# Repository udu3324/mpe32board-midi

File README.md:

# mpe32board-midi

An expressive midi controller that has onboard sound processing with an expandable and hackable nature.
(v2 of [stm32pe-midi](https://github.com/udu3324/stm32pe-midi))

 * Built in DSP
 * Support for Programs and Sequencer
 * Hacker Header Exposed GPIO
 * Micro-SD Card Support
 * Onboard SDRAM for extended recording/memory

## Purpose
After making the [stm32pe-midi](https://github.com/udu3324/stm32pe-midi), I wanted to reflect at the problems I faced and the feature set I sacrificed out of it originally. I wanted to learn how ram works and the correct way to implement it, which I did for this project. I also wanted something that was more polished and structured better as the pcb dictated the rest of the design which lead to unfortunate design decisions. I instead designed everything in module-like components to allow more expansion and flexibility in the future.

## Zine Page
Some information is redacted on this export, DM me for the full version!

## Firmware
The firmware uses the stm32cubemx software to generate a .ioc of its pinout functions and its cmake gcc code template. I then chose Visual Studio Code as the choice of my IDE to code the rest in C/C++.

There is sample code [here](https://gist.github.com/udu3324/de9aada8e3ea0addc13870c6bbbebc0f) for trying out the mpe32sensors standalone on the Arduino platform.

### Libraries Used
 * https://github.com/hathach/tinyusb
 * https://github.com/jtainer/i2c-mux
 * https://github.com/berndoJ/libneopixel32
 * https://github.com/devOramaMan/stm32_TMAG5273 (modified/fixed)
 * https://github.com/alixahedi/i2c-lcd-stm32

## CAD
### Case
The case is a 3 part 3d-printed case that is screwed together with m3 screws, both being self-tapped and heat-set inserts. There are two wood block accents (or plywood) on the side screwed in too.

Each key is press fit and can also be screwed in with a m3 screw and nut if needed.

Due to my 3d-printer being too small, I have to cut the board in half to print. This is later adhered with uv-glue.

### Keys
The keys are compliant mechanisms that are designed to be 3d-printed with the least amount of post-processing. The flexure allows the key to move up and down as well as twist to allow pitch shifting.

Another printed piece is included to hold down and fix the stm32sensor pcb in place.

## PCB
I split my design into two boards. One being the "motherboard" called the stm32board which connects everything and has the mcu/ram/jtag for central control. The other is the sensor boards called the stm32sensor which connects through one of the 24 JST-SH-4x connectors that are on their own i2c line.

### stm32[board]

### stm32[sensor]

## BOM
The Bill of Materials can be viewed [here](https://docs.google.com/spreadsheets/d/1Ah6NNKW-CTIdOJtxNPdxd3ZnzDfgMl2LX2XapnXmrVo/edit).

### Build Steps
1. Get all materials ready and 3d printed
2. Post-process any 3d-prints if needed and insert heat set inserts for m3 screws
3. Assemble the pcb if not PCBA
4. Assemble all sensor boards into key housings and holder
5. Add LCD to stm32board and solder onto header
6. Assemble all keys and stm32board onto case, while also wire routing carefully
7. Screw on accent wood blocks
8. Flash firmware onto board
9. Done! Plug and play into your host device and favorite DAW

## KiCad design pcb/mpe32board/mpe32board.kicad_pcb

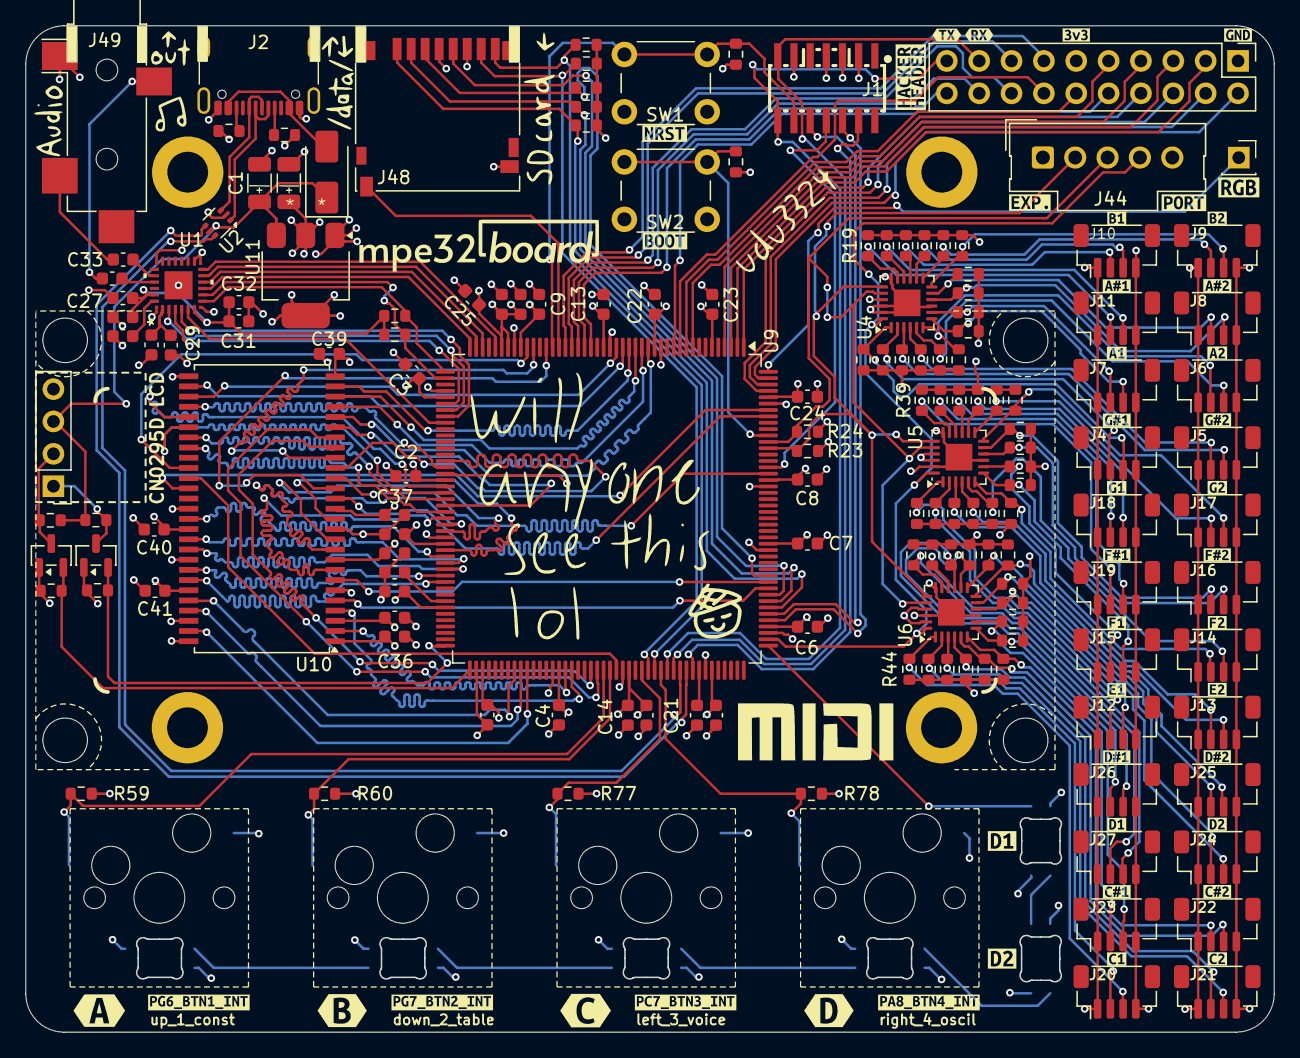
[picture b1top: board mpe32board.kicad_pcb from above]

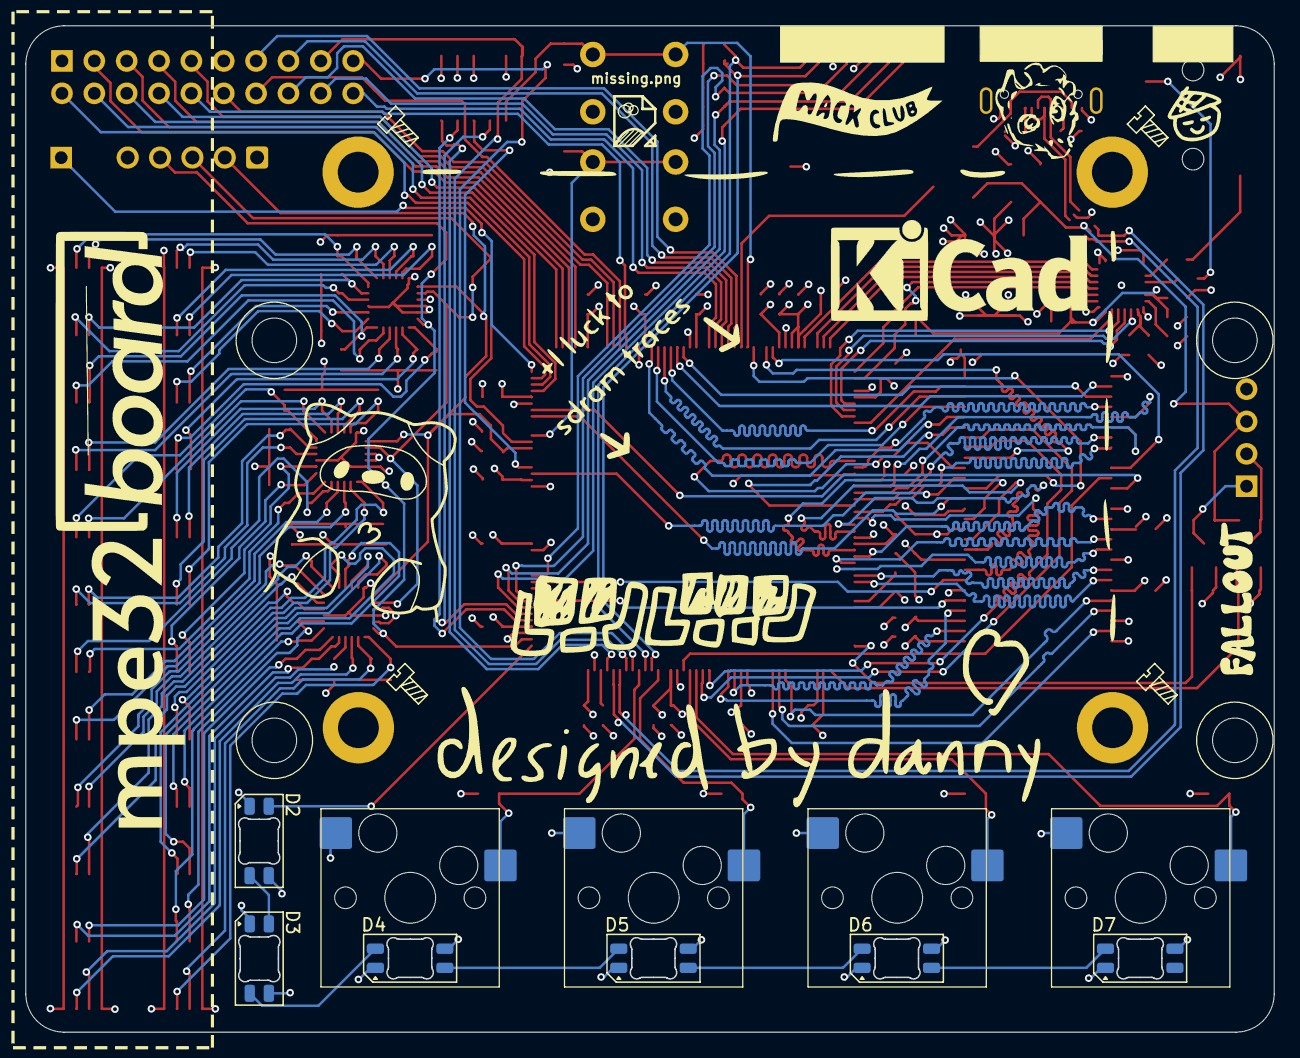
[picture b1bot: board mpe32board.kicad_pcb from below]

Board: 4 copper layers, 98.0 x 79.0 mm, 213 parts (10 on the bottom side), 164 nets.

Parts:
C1, C42: 10μF; C_1206_3216Metric
C2, C3, C4, C5, C6, C7, C8, C9, C10, C11, C12, C13, C14, C17, C22, C23, C24, C25, C35, C36, C37, C38, C39, C40, C41: 100nF; C_0603_1608Metric
C15, C16: 2.2μF; C_0603_1608Metric
C21, C28, C43: 1μF; C_0603_1608Metric
C26, C30, C32: 10μF; C_0603_1608Metric
C27, C29, C31: 0.1μF; C_0603_1608Metric
C33, C34: 47μF; C_0603_1608Metric
CN0295D LCD: CN0295D
D1: SS14; D_SMA
D2, D3, D4, D5, D6, D7: SK6812MINI-E; LED_SK6812MINI-E_3.2x2.8mm_P1.5mm_ReverseMount
H1, H2, H3, H4: MountingHole_Pad; MountingHole_3.2mm_M3_DIN965_Pad
J1: Conn_ST_STDC14; CONN-SMD_14P-P1.27_FTSH-107-01-F-DV-K-P-TR
J2: USB_C_Receptacle_USB2.0_16P; USB_C_Receptacle_GCT_USB4105-xx-A_16P_TopMnt_Horizontal
J3: Conn_01x01_Socket; PinSocket_1x01_P2.54mm_Vertical
J4, J5, J6, J7, J8, J9, J10, J11, J12, J13, J14, J15, J16, J17, J18, J19, J20, J21, J22, J23, J24, J25, J26, J27: Conn_01x04; JST_SH_BM04B-SRSS-TB_1x04-1MP_P1.00mm_Vertical
J44: Conn_01x05; Molex_SL_171971-0005_1x05_P2.54mm_Vertical
J45: Conn_01x04_Socket; PinHeader_1x04_P2.54mm_Vertical
J46: Conn_02x10_Counter_Clockwise; PinHeader_2x10_P2.54mm_Vertical
J48: Micro_SD_Card_Det_Hirose_DM3AT; microSD_HC_Hirose_DM3D-SF
J49: AudioJack3_SwitchT; Jack_3.5mm_CUI_SJ-3524-SMT_Horizontal
Q1, Q2: BSS138; SOT-23
R1, R2, R21, R22, R23, R24, R59, R60, R77, R78, R100, R101: 10kΩ; R_0603_1608Metric
R3, R4: 5.1kΩ; R_0603_1608Metric
R5, R6, R7, R8, R9, R10, R11, R12, R13, R14, R15, R16, R17, R18, R19, R20, R25, R26, R27, R28, R29, R30, R31, R32, R33, R34, R35, R36, R37, R38, R39, R40, R43, R44, R45, R46, R47, R48, R49, R50, R51, R52, R53, R54, R55, R56, R57, R58: 2.2kΩ; R_0603_1608Metric
R41, R42: 1kΩ; R_0603_1608Metric
R95, R96, R97, R98, R99: 47kΩ; R_0603_1608Metric
SW1, SW2: SW_Push; SW_PUSH_6mm
SW3, SW4, SW5, SW6: SW_Push; MX-Hotswap-1U
U1: TAC5212IRGER; VQFN24_RGE_CORNERPADS_TEX-L
U2: USBLC6-2P6; SOT-666
U4, U5, U6: TCA9548ARGER; Texas_RGE0024C_VQFN-24-1EP_4x4mm_P0.5mm_EP2.1x2.1mm
U9: STM32H743IITx; LQFP-176_24x24mm_P0.5mm
U10: W9812G6KH-75; TSOP-II-54_22.2x10.16mm_P0.8mm
U11: LM1117MP-3.3; SOT-223-3_TabPin2
kibuzzard-6A0A0E58: G***; kibuzzard-6A0A0E58
kibuzzard-6A0A0E61: G***; kibuzzard-6A0A0E61
kibuzzard-6A0A0E69: G***; kibuzzard-6A0A0E69
kibuzzard-6A0A0E77: G***; kibuzzard-6A0A0E77
kibuzzard-6A0A0F62: G***; kibuzzard-6A0A0F62
kibuzzard-6A0A0F87: G***; kibuzzard-6A0A0F87
kibuzzard-6A0A106B: G***; kibuzzard-6A0A106B
kibuzzard-6A0A124F: G***; kibuzzard-6A0A124F
kibuzzard-6A0A127D: G***; kibuzzard-6A0A127D
kibuzzard-6A0A1170: G***; kibuzzard-6A0A1170
kibuzzard-6A06ADD4: G***; kibuzzard-6A06ADD4
kibuzzard-6A06ADDB: G***; kibuzzard-6A06ADDB
kibuzzard-6A06ADE0: G***; kibuzzard-6A06ADE0
kibuzzard-6A06B0BE: G***; kibuzzard-6A06B0BE
kibuzzard-6A06B0F2: G***; kibuzzard-6A06B0F2
kibuzzard-6A06B37C: G***; kibuzzard-6A06B37C
kibuzzard-6A06B118: G***; kibuzzard-6A06B118
kibuzzard-6A06B135: G***; kibuzzard-6A06B135
kibuzzard-6A06B367: G***; kibuzzard-6A06B367
kibuzzard-6A0925D0: G***; kibuzzard-6A0925D0
kibuzzard-69FF71B5: G***; kibuzzard-69FF71B5
kibuzzard-69FF71C5: G***; kibuzzard-69FF71C5
kibuzzard-69FF71DB: G***; kibuzzard-69FF71DB
kibuzzard-69FF71E0: G***; kibuzzard-69FF71E0
kibuzzard-69FF72BF: G***; kibuzzard-69FF72BF
kibuzzard-69FF72C5: G***; kibuzzard-69FF72C5
kibuzzard-69FF72D8: G***; kibuzzard-69FF72D8
kibuzzard-69FF72DF: G***; kibuzzard-69FF72DF
kibuzzard-69FF72F7: G***; kibuzzard-69FF72F7
kibuzzard-69FF72FD: G***; kibuzzard-69FF72FD
kibuzzard-69FF73DD: G***; kibuzzard-69FF73DD
kibuzzard-69FF710F: G***; kibuzzard-69FF710F
kibuzzard-69FF713D: G***; kibuzzard-69FF713D
kibuzzard-69FF717D: G***; kibuzzard-69FF717D
kibuzzard-69FF719E: G***; kibuzzard-69FF719E
kibuzzard-69FF730D: G***; kibuzzard-69FF730D
kibuzzard-69FF732F: G***; kibuzzard-69FF732F
kibuzzard-69FF7163: G***; kibuzzard-69FF7163
kibuzzard-69FF7167: G***; kibuzzard-69FF7167
kibuzzard-69FF7176: G***; kibuzzard-69FF7176
kibuzzard-69FF7195: G***; kibuzzard-69FF7195
kibuzzard-69FF7319: G***; kibuzzard-69FF7319
kibuzzard-69FF7327: G***; kibuzzard-69FF7327
kibuzzard-69FF7392: G***; kibuzzard-69FF7392

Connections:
0_SC0: J4.2, R5.1, U4.2 (SC0)
0_SD0: J4.3, R6.1, U4.1 (SD0)
1_SC1: J5.2, R7.1, U4.4 (SC1)
1_SD1: J5.3, R8.1, U4.3 (SD1)
2_SC2: J6.2, R9.1, U4.6 (SC2)
2_SD2: J6.3, R10.1, U4.5 (SD2)
3_SC3: J7.2, R11.1, U4.8 (SC3)
3_SD3: J7.3, R12.1, U4.7 (SD3)
4_SC4: J8.2, R13.1, U4.11 (SC4)
4_SD4: J8.3, R14.1, U4.10 (SD4)
5_SC5: J9.2, R15.1, U4.13 (SC5)
5_SD5: J9.3, R16.1, U4.12 (SD5)
6_SC6: J10.2, R17.1, U4.15 (SC6)
6_SD6: J10.3, R18.1, U4.14 (SD6)
7_SC7: J11.2, R19.1, U4.17 (SC7)
7_SD7: J11.3, R20.1, U4.16 (SD7)
8_SC0: J12.2, R25.1, U5.2 (SC0)
8_SD0: J12.3, R26.1, U5.1 (SD0)
9_SC1: J13.2, R27.1, U5.4 (SC1)
9_SD1: J13.3, R28.1, U5.3 (SD1)
10_SC2: J14.2, R29.1, U5.6 (SC2)
10_SD2: J14.3, R30.1, U5.5 (SD2)
11_SC3: J15.2, R31.1, U5.8 (SC3)
11_SD3: J15.3, R32.1, U5.7 (SD3)
12_SC4: J16.2, R33.1, U5.11 (SC4)
12_SD4: J16.3, R34.1, U5.10 (SD4)
13_SC5: J17.2, R35.1, U5.13 (SC5)
13_SD5: J17.3, R36.1, U5.12 (SD5)
14_SC6: J18.2, R37.1, U5.15 (SC6)
14_SD6: J18.3, R38.1, U5.14 (SD6)
15_SC7: J19.2, R39.1, U5.17 (SC7)
15_SD7: J19.3, R40.1, U5.16 (SD7)
16_SC0: J20.2, R43.1, U6.2 (SC0)
16_SD0: J20.3, R44.1, U6.1 (SD0)
17_SC1: J21.2, R45.1, U6.4 (SC1)
17_SD1: J21.3, R46.1, U6.3 (SD1)
18_SC2: J22.2, R47.1, U6.6 (SC2)
18_SD2: J22.3, R48.1, U6.5 (SD2)
19_SC3: J23.2, R49.1, U6.8 (SC3)
19_SD3: J23.3, R50.1, U6.7 (SD3)
20_SC4: J24.2, R51.1, U6.11 (SC4)
20_SD4: J24.3, R52.1, U6.10 (SD4)
21_SC5: J25.2, R53.1, U6.13 (SC5)
21_SD5: J25.3, R54.1, U6.12 (SD5)
22_SC6: J26.2, R55.1, U6.15 (SC6)
22_SD6: J26.3, R56.1, U6.14 (SD6)
23_SC7: J27.2, R57.1, U6.17 (SC7)
23_SD7: J27.3, R58.1, U6.16 (SD7)
+3V3: C2.1, C3.1, C4.1, C5.1, C6.1, C7.1, C8.1, C9.1, C10.1, C11.1, C12.1, C13.1, C14.1, C17.1, C21.1, C22.1, C23.1, C24.1, C25.1, C35.1, C36.1, C37.1, C38.1, C39.1, C40.1, C41.1, C42.1, C43.1, D2.3 (VDD), D3.3 (VDD), D4.3 (VDD), D5.3 (VDD), D6.3 (VDD), D7.3 (VDD), J1.3 (VCC), J4.1, J5.1, J6.1, J7.1, J8.1, J9.1, J10.1, J11.1, J12.1, J13.1, J14.1, J15.1, J16.1, J17.1, J18.1, J19.1, J20.1, J21.1, J22.1, J23.1, J24.1, J25.1, J26.1, J27.1, J44.1, J46.11, J48.4 (VDD), Q1.1 (G), Q2.1 (G), R2.2, R5.2, R6.2, R7.2, R8.2, R9.2, R10.2, R11.2, R12.2, R13.2, R14.2, R15.2, R16.2, R17.2, R18.2, R19.2, R20.2, R21.1, R23.2, R24.2, R25.2, R26.2, R27.2, R28.2, R29.2, R30.2, R31.2, R32.2, R33.2, R34.2, R35.2, R36.2, R37.2, R38.2, R39.2, R40.2, R43.2, R44.2, R45.2, R46.2, R47.2, R48.2, R49.2, R50.2, R51.2, R52.2, R53.2, R54.2, R55.2, R56.2, R57.2, R58.2, R95.1, R96.1, R97.1, R98.1, R99.1, R100.1, SW2.2, SW3.2, SW4.2, SW5.2, SW6.2, U4.21 (VCC), U5.21 (VCC), U5.22 (A0), U6.21 (VCC), U6.23 (A1), U9.6 (VBAT), U9.15 (VDD), U9.23 (VDD), U9.36 (VDD), U9.38 (VREF+), U9.39 (VDDA), U9.49 (VDD), U9.62 (VDD), U9.72 (VDD), U9.82 (VDD), U9.91 (VDD), U9.103 (VDD), U9.114 (VDD33_USB), U9.127 (VDD), U9.136 (VDD), U9.149 (VDD), U9.159 (VDD), U9.172 (VDD), U10.1 (VDD), U10.3 (VDDQ), U10.9 (VDDQ), U10.14 (VDD), U10.27 (VDD), U10.43 (VDDQ), U10.49 (VDDQ), U11.2 (VO)
+5V: C1.1, D1.1 (K), J45.3, R22.2, R101.2, U2.5 (VBUS), U11.3 (VI)
AVDD: C26.1, C27.1, C31.1, C32.1, R41.2, R42.2, U1.6 (IOVDD), U1.23 (AVDD)
BOOT0: R1.1, SW2.1, U9.166 (BOOT0)
BTN1_INTERNAL: R59.1, SW3.1, U9.110 (PG6)
BTN2_INTERNAL: R60.1, SW4.1, U9.111 (PG7)
BTN3_INTERNAL: R77.1, SW5.1, U9.116 (PC7)
BTN4_INTERNAL: R78.1, SW6.1, U9.119 (PA8)
DREG: C29.1, C30.1, U1.1 (DREG)
FMC_A0: U9.16 (PF0), U10.23 (A0)
FMC_A1: U9.17 (PF1), U10.24 (A1)
FMC_A2: U9.18 (PF2), U10.25 (A2)
FMC_A3: U9.19 (PF3), U10.26 (A3)
FMC_A4: U9.20 (PF4), U10.29 (A4)
FMC_A5: U9.21 (PF5), U10.30 (A5)
FMC_A6: U9.60 (PF12), U10.31 (A6)
FMC_A7: U9.63 (PF13), U10.32 (A7)
FMC_A8: U9.64 (PF14), U10.33 (A8)
FMC_A9: U9.65 (PF15), U10.34 (A9)
FMC_A10: U9.66 (PG0), U10.22 (A10/AP)
FMC_A11: U9.67 (PG1), U10.35 (A11)
FMC_BA0: U9.108 (PG4), U10.20 (BS0)
FMC_BA1: U9.109 (PG5), U10.21 (BS1)
FMC_D0: U9.104 (PD14), U10.2 (DQ0)
FMC_D1: U9.105 (PD15), U10.4 (DQ1)
FMC_D2: U9.142 (PD0), U10.5 (DQ2)
FMC_D3: U9.143 (PD1), U10.7 (DQ3)
FMC_D4: U9.68 (PE7), U10.8 (DQ4)
FMC_D5: U9.69 (PE8), U10.10 (DQ5)
FMC_D6: U9.70 (PE9), U10.11 (DQ6)
FMC_D7: U9.73 (PE10), U10.13 (DQ7)
FMC_D8: U9.74 (PE11), U10.42 (DQ8)
FMC_D9: U9.75 (PE12), U10.44 (DQ9)
FMC_D10: U9.76 (PE13), U10.45 (DQ10)
FMC_D11: U9.77 (PE14), U10.47 (DQ11)
FMC_D12: U9.78 (PE15), U10.48 (DQ12)
FMC_D13: U9.96 (PD8), U10.50 (DQ13)
FMC_D14: U9.97 (PD9), U10.51 (DQ14)
FMC_D15: U9.98 (PD10), U10.53 (DQ15)
FMC_NBL0: U9.169 (PE0), U10.15 (LDQM)
FMC_NBL1: U9.170 (PE1), U10.39 (UDQM)
FMC_SDCKE0: U9.35 (PC3_C), U10.37 (CKE)
FMC_SDCLK: U9.112 (PG8), U10.38 (CLK)
FMC_SDNCAS: U9.160 (PG15), U10.17 (~CAS)
FMC_SDNE0: U9.34 (PC2_C), U10.19 (~CS)
FMC_SDNRAS: U9.59 (PF11), U10.18 (~RAS)
FMC_SDNWE: U9.32 (PC0), U10.16 (~WE)
GND: C1.2, C2.2, C3.2, C4.2, C5.2, C6.2, C7.2, C8.2, C9.2, C10.2, C11.2, C12.2, C13.2, C14.2, C15.2, C16.2, C17.2, C21.2, C22.2, C23.2, C24.2, C25.2, C26.2, C27.2, C28.2, C29.2, C30.2, C31.2, C32.2, C35.2, C36.2, C37.2, C38.2, C39.2, C40.2, C41.2, C42.2, C43.2, D2.1 (VSS), D3.1 (VSS), D4.1 (VSS), D5.1 (VSS), D6.1 (VSS), D7.1 (VSS), H1.1 (1_1), H2.1 (1_1), H3.1 (1_1), H4.1 (1_1), J1.5 (GND), J1.7 (GND), J1.11 (GNDDetect), J2.A1 (GND), J2.A12 (GND), J2.B1 (GND), J2.B12 (GND), J4.4, J5.4, J6.4, J7.4, J8.4, J9.4, J10.4, J11.4, J12.4, J13.4, J14.4, J15.4, J16.4, J17.4, J18.4, J19.4, J20.4, J21.4, J22.4, J23.4, J24.4, J25.4, J26.4, J27.4, J44.5, J45.4, J46.1, J48.6 (VSS), J48.9 (DET_B), J49.S, R1.2, R3.2, R4.2, R59.2, R60.2, R77.2, R78.2, SW1.2, U1.13 (ADDR), U1.29 (EPAD), U1.A1 (VSS), U1.A2 (VSS), U1.A3 (VSS), U1.A4 (VSS), U2.2 (GND), U4.9 (GND), U4.18 (A2), U4.22 (A0), U4.23 (A1), U5.9 (GND), U5.18 (A2), U5.23 (A1), U6.9 (GND), U6.18 (A2), U6.22 (A0), U9.14 (VSS), U9.22 (VSS), U9.37 (VSSA), U9.48 (VSS), U9.61 (VSS), U9.71 (VSS), U9.90 (VSS), U9.102 (VSS), U9.113 (VSS), U9.126 (VSS), U9.135 (VSS), U9.148 (VSS), U9.158 (VSS), U9.171 (PDR_ON), U10.6 (VSSQ), U10.12 (VSSQ), U10.28 (VSS), U10.41 (VSS), U10.46 (VSSQ), U10.52 (VSSQ), U10.54 (VSS), U11.1 (GND)
GPIO_PC14: J46.9, U9.9 (PC14)
GPIO_PC15: J46.12, U9.10 (PC15)
GPIO_PE2: J46.8, U9.1 (PE2)
GPIO_PE3: J46.3, U9.2 (PE3)
GPIO_PE4: J46.5, U9.3 (PE4)
GPIO_PE5: J46.7, U9.4 (PE5)
GPIO_PF7: J46.20, U9.25 (PF7)
GPIO_PF8: J46.18, U9.26 (PF8)
GPIO_PF9: J46.16, U9.27 (PF9)
GPIO_PF10: J46.15, U9.28 (PF10)
GPIO_PH0: J46.13, U9.29 (PH0)
GPIO_PI4: J46.6, U9.173 (PI4)
GPIO_PI5: J46.4, U9.174 (PI5)
GPIO_PI6: J46.2, U9.175 (PI6)
GPIO_PI9: J46.14, U9.11 (PI9)
GPIO_PI10: J46.10, U9.12 (PI10)
I2C1_SCL: J44.2, R23.1, U4.19 (SCL), U5.19 (SCL), U6.19 (SCL), U9.164 (PB6)
I2C1_SDA: J44.3, R24.1, U4.20 (SDA), U5.20 (SDA), U6.20 (SDA), U9.165 (PB7)
I2C2_SCL: R41.1, U1.7 (SCL), U9.45 (PH4)
I2C2_SDA: R42.1, U1.8 (SDA), U9.46 (PH5)
I2C4_SCL: Q1.2 (S), R21.2, U9.88 (PH11)
I2C4_SCL_5V: J45.1, Q1.3 (D), R22.1
I2C4_SDA: Q2.2 (S), R100.2, U9.89 (PH12)
I2C4_SDA_5V: J45.2, Q2.3 (D), R101.1
I2S1_CK: U1.2 (BCLK), U9.51 (PA5)
I2S1_SDI: U1.4 (DOUT), U9.52 (PA6)
I2S1_SDO: U1.5 (DIN), U9.53 (PA7)
I2S1_WS: U1.3 (FSYNC), U9.50 (PA4)
JTDI: J1.10 (JTDI/NC), U9.138 (PA15)
JTDO: J1.8 (JTDO/SWO), U9.161 (PB3)
LPUART1_RX: J1.13 (VCP_RX), J46.17, U9.121 (PA10)
LPUART1_TX: J1.14 (VCP_TX), J46.19, U9.120 (PA9)
L_CHANNEL: C33.2, J49.T
NEOPIXEL_IN: J3.1 (Pin_1_1), U9.176 (PI7)
NEOPIXEL_INTERNAL: D2.2 (DIN), U9.133 (PI2)
NRST: J1.12 (~RST), R2.1, SW1.1, U9.31 (NRST)
unnamed: C15.1, U9.81 (VCAP)
unnamed: C16.1, U9.125 (VCAP)
unnamed: D1.2 (A), J2.A4 (VBUS), J2.A9 (VBUS), J2.B4 (VBUS), J2.B9 (VBUS)
unnamed: D2.4 (DOUT), D3.2 (DIN)
unnamed: D3.4 (DOUT), D4.2 (DIN)
unnamed: D4.4 (DOUT), D5.2 (DIN)
unnamed: D5.4 (DOUT), D6.2 (DIN)
unnamed: D6.4 (DOUT), D7.2 (DIN)
unnamed: J2.A5 (CC1), R3.1
unnamed: J2.B5 (CC2), R4.1
unnamed: J2.A6 (D+), J2.B6 (D+), U2.3 (I/O2)
unnamed: J2.A7 (D-), J2.B7 (D-), U2.1 (I/O1)
unnamed: C33.1, U1.20 (OUT1P)
unnamed: C34.1, U1.21 (OUT2P)
OTG_FS_DN: U2.6 (I/O1), U9.122 (PA11)
OTG_FS_DP: U2.4 (I/O2), U9.123 (PA12)
RESET_0: J44.4, U4.24 (~RESET), U5.24 (~RESET), U6.24 (~RESET), U9.134 (PI3)
R_CHANNEL: C34.2, J49.R
SDCARD_DET: J48.10 (DET_A), U9.30 (PH1)
SDMMC1_CK: J48.5 (CLK), U9.141 (PC12)
SDMMC1_CMD: J48.3 (CMD), R95.2, U9.144 (PD2)
SDMMC1_D0: J48.7 (DAT0), R98.2, U9.117 (PC8)
SDMMC1_D1: J48.8 (DAT1), R99.2, U9.118 (PC9)
SDMMC1_D2: J48.1 (DAT2), R96.2, U9.139 (PC10)
SDMMC1_D3: J48.2 (DAT3/CD), R97.2, U9.140 (PC11)
SWCLK: J1.6 (JCLK/SWCLK), U9.137 (PA14)
SWDIO: J1.4 (JTMS/SWDIO), U9.124 (PA13)
TAC5212_GPI1: U1.12 (GPI1), U9.40 (PA0)
TAC5212_GPIO1: U1.9 (GPIO1), U9.44 (PH3)
TAC5212_GPIO2: U1.10 (GPIO2), U9.43 (PH2)
TAC5212_GPO1: U1.11 (GPO1), U9.42 (PA2)
VREF: C28.1, U1.24 (VREF)

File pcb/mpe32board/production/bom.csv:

Designator,Footprint,Quantity,Value,LCSC Part #
"C1, C42",1206,2,10μF,
"C10, C11, C12, C13, C14, C17, C2, C22, C23, C24, C25, C3, C35, C36, C37, C38, C39, C4, C40, C41, C5, C6, C7, C8, C9",0603,25,100nF,
"C15, C16",0603,2,2.2μF,
"C21, C28, C43",0603,3,1μF,
"C26, C30, C32",0603,3,10μF,
"C27, C29, C31",0603,3,0.1μF,
"C33, C34",0603,2,47μF,
CN0295D LCD,CN0295D,1,CN0295D,
D1,D_SMA,1,SS14,
"D2, D3, D4, D5, D6, D7",LED_SK6812MINI-E_3.2x2.8mm_P1.5mm_ReverseMount,6,SK6812MINI-E,
J1,CONN-SMD_14P-P1.27_FTSH-107-01-F-DV-K-P-TR,1,Conn_ST_STDC14,
"J10, J11, J12, J13, J14, J15, J16, J17, J18, J19, J20, J21, J22, J23, J24, J25, J26, J27, J4, J5, J6, J7, J8, J9",JST_SH_BM04B-SRSS-TB_1x04-1MP_P1.00mm_Vertical,24,Conn_01x04,
J2,USB_C_Receptacle_GCT_USB4105-xx-A_16P_TopMnt_Horizontal,1,USB_C_Receptacle_USB2.0_16P,
J3,PinSocket_1x01_P2.54mm_Vertical,1,Conn_01x01_Socket,
J44,Molex_SL_171971-0005_1x05_P2.54mm_Vertical,1,Conn_01x05,
J45,PinHeader_1x04_P2.54mm_Vertical,1,Conn_01x04_Socket,
J46,PinHeader_2x10_P2.54mm_Vertical,1,Conn_02x10_Counter_Clockwise,
J48,microSD_HC_Hirose_DM3D-SF,1,Micro_SD_Card_Det_Hirose_DM3AT,
J49,Jack_3.5mm_CUI_SJ-3524-SMT_Horizontal,1,AudioJack3_SwitchT,
"Q1, Q2",SOT-23,2,BSS138,
"R1, R100, R101, R2, R21, R22, R23, R24, R59, R60, R77, R78",0603,12,10kΩ,
"R10, R11, R12, R13, R14, R15, R16, R17, R18, R19, R20, R25, R26, R27, R28, R29, R30, R31, R32, R33, R34, R35, R36, R37, R38, R39, R40, R43, R44, R45, R46, R47, R48, R49, R5, R50, R51, R52, R53, R54, R55, R56, R57, R58, R6, R7, R8, R9",0603,48,2.2kΩ,
"R3, R4",0603,2,5.1kΩ,
"R41, R42",0603,2,1kΩ,
"R95, R96, R97, R98, R99",0603,5,47kΩ,
"SW1, SW2",SW_PUSH_6mm,2,SW_Push,
"SW3, SW4, SW5, SW6",MX-Hotswap-1U,4,SW_Push,
U1,VQFN24_RGE_CORNERPADS_TEX-L,1,TAC5212IRGER,
U10,TSOP-II-54_22.2x10.16mm_P0.8mm,1,W9812G6KH-75,
U11,SOT-223-3_TabPin2,1,LM1117MP-3.3,
U2,SOT-666,1,USBLC6-2P6,
"U4, U5, U6",Texas_RGE0024C_VQFN-24-1EP_4x4mm_P0.5mm_EP2.1x2.1mm,3,TCA9548ARGER,
U9,LQFP-176_24x24mm_P0.5mm,1,STM32H743IITx,

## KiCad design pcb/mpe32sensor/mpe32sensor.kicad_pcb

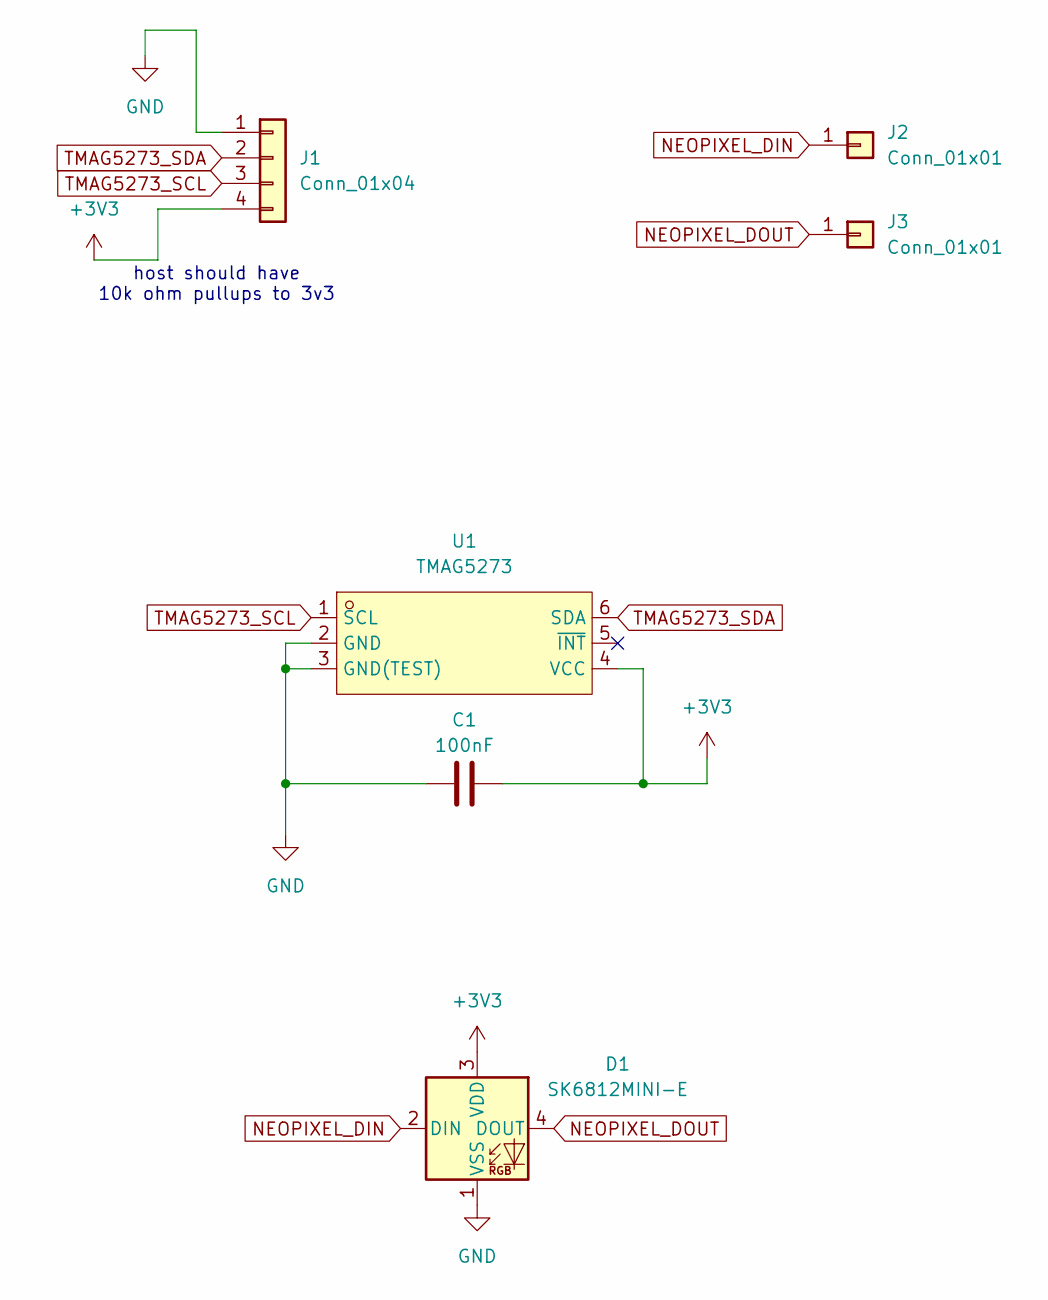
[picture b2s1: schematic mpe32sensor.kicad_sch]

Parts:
C1: 100nF; C_0603_1608Metric; MPN 100nF 0603 X7R
D1: SK6812MINI-E; LED_SK6812MINI-E_3.2x2.8mm_P1.5mm_ReverseMount; MPN SK6812MINI-E OPSCO Optoelectronics C514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
J1: Conn_01x04; JST_SH_SM04B-SRSS-TB_1x04-1MP_P1.00mm_Horizontal; MPN SM04B-SRSS-TB
J2, J3: Conn_01x01; PinSocket_1x01_P2.54mm_Horizontal; MPN DNP
U1: TMAG5273; SOT-23-6; MPN TMAG5273A1; LCSC Part C3716049

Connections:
+3V3: C1.2, D1.3 (VDD), J1.4, U1.4 (VCC)
GND: C1.1, D1.1 (VSS), J1.1, U1.2 (GND), U1.3 (GND(TEST))
NEOPIXEL_DIN: D1.2 (DIN), J2.1 (Pin_1_1)
NEOPIXEL_DOUT: D1.4 (DOUT), J3.1 (Pin_1_1)
TMAG5273_SCL: J1.3, U1.1 (SCL)
TMAG5273_SDA: J1.2, U1.6 (SDA)

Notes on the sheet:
host should have 10k ohm pullups to 3v3

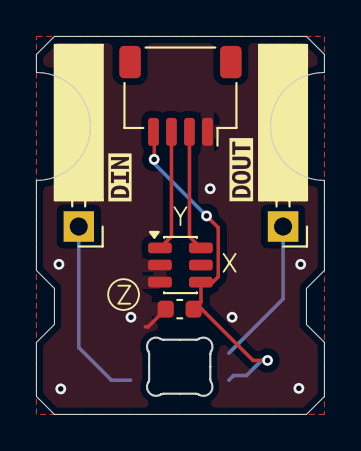
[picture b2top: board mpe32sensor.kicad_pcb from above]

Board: 2 copper layers, 16.0 x 21.0 mm, 8 parts (1 on the bottom side), 6 nets.

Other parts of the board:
kibuzzard-6A0A33B3: G***; kibuzzard-6A0A33B3
kibuzzard-6A0A338E: G***; kibuzzard-6A0A338E

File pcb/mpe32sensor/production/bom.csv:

Designator,Footprint,Quantity,Value,LCSC Part #
C1,0603,1,100nF,100nF 0603 X7R 
D1,LED_SK6812MINI-E_3.2x2.8mm_P1.5mm_ReverseMount,1,SK6812MINI-E,SK6812MINI-E-012
J1,JST_SH_SM04B-SRSS-TB_1x04-1MP_P1.00mm_Horizontal,1,Conn_01x04,SM04B-SRSS-TB
"J2, J3",PinSocket_1x01_P2.54mm_Horizontal,2,Conn_01x01,DNP
U1,SOT-23-6,1,TMAG5273,C3716049

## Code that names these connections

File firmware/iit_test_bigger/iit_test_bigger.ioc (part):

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Mcu.Name=STM32H743IITx
Mcu.Package=LQFP176
Mcu.UserName=STM32H743IITx
PA0.Signal=GPIO_Output
PA10.Mode=Asynchronous
PA10.Signal=LPUART1_RX
PA11.Mode=Device_Only
PA11.Signal=USB_OTG_FS_DM
PA12.Mode=Device_Only
PA12.Signal=USB_OTG_FS_DP
PA13\ (JTMS/SWDIO).Mode=Serial_Wire
PA13\ (JTMS/SWDIO).Signal=DEBUG_JTMS-SWDIO
PA14\ (JTCK/SWCLK).Mode=Serial_Wire
PA14\ (JTCK/SWCLK).Signal=DEBUG_JTCK-SWCLK
PA15\ (JTDI).Signal=DEBUG_JTDI
PA2.Signal=GPIO_Input
PA4.Mode=Full_Duplex_Master
PA4.Signal=I2S1_WS
PA6.Mode=Full_Duplex_Master
PA6.Signal=I2S1_SDI
PA7.Mode=Full_Duplex_Master
PA7.Signal=I2S1_SDO
PA8.Signal=GPIO_Input
PA9.Mode=Asynchronous
PA9.Signal=LPUART1_TX
PB3\ (JTDO/TRACESWO).Signal=DEBUG_JTDO-SWO
PB6.Mode=I2C
PB6.Signal=I2C1_SCL
PB7.Mode=I2C
PB7.Signal=I2C1_SDA
PC0.Signal=FMC_SDNWE
PC10.Mode=SD_4_bits_Wide_bus
PC10.Signal=SDMMC1_D2
PC11.Mode=SD_4_bits_Wide_bus
PC11.Signal=SDMMC1_D3
PC12.Mode=SD_4_bits_Wide_bus
PC12.Signal=SDMMC1_CK
PC14-OSC32_IN\ (OSC32_IN).Signal=GPIO_Output
PC15-OSC32_OUT\ (OSC32_OUT).Signal=GPIO_Output
PC2_C.Mode=SdramChipSelect1_1
PC2_C.Signal=FMC_SDNE0
PC3_C.Mode=SdramChipSelect1_1
PC3_C.Signal=FMC_SDCKE0
PC7.Signal=GPIO_Input
PC8.Mode=SD_4_bits_Wide_bus
PC8.Signal=SDMMC1_D0
PC9.Mode=SD_4_bits_Wide_bus
PC9.Signal=SDMMC1_D1
PD0.Signal=FMC_D2_DA2
PD1.Signal=FMC_D3_DA3
PD10.Signal=FMC_D15_DA15
PD14.Signal=FMC_D0_DA0
PD15.Signal=FMC_D1_DA1
PD2.Mode=SD_4_bits_Wide_bus
PD2.Signal=SDMMC1_CMD
PD8.Signal=FMC_D13_DA13
PD9.Signal=FMC_D14_DA14
PE0.Signal=FMC_NBL0
PE1.Signal=FMC_NBL1
PE10.Signal=FMC_D7_DA7
PE11.Signal=FMC_D8_DA8
PE12.Signal=FMC_D9_DA9
PE13.Signal=FMC_D10_DA10
PE14.Signal=FMC_D11_DA11
PE15.Signal=FMC_D12_DA12
PE2.Signal=GPIO_Output
PE3.Signal=GPIO_Output
PE4.Signal=GPIO_Output
PE5.Signal=GPIO_Output
PE7.Signal=FMC_D4_DA4
PE8.Signal=FMC_D5_DA5
PE9.Signal=FMC_D6_DA6
PF0.Signal=FMC_A0
PF1.Signal=FMC_A1
PF10.Signal=GPIO_Output
PF11.Signal=FMC_SDNRAS
PF12.Signal=FMC_A6
PF13.Signal=FMC_A7
PF14.Signal=FMC_A8
PF15.Signal=FMC_A9
PF2.Signal=FMC_A2
PF3.Signal=FMC_A3
PF4.Signal=FMC_A4
PF5.Signal=FMC_A5
PF7.Signal=GPIO_Output
PF8.Signal=GPIO_Output
PF9.Signal=GPIO_Output
PG0.Signal=FMC_A10
PG1.Signal=FMC_A11
PG11.Mode=Full_Duplex_Master
PG11.Signal=I2S1_CK
PG15.Signal=FMC_SDNCAS
PG4.Signal=FMC_A14_BA0
PG5.Signal=FMC_A15_BA1
PG6.Signal=GPIO_Input
PG7.Signal=GPIO_Input
PG8.Signal=FMC_SDCLK
PH0-OSC_IN\ (PH0).Signal=GPIO_Output
PH1-OSC_OUT\ (PH1).Signal=GPIO_Input
PH11.Mode=I2C
PH11.Signal=I2C4_SCL
PH12.Mode=I2C
PH12.Signal=I2C4_SDA
PH2.Signal=GPIO_Output
PH3.Signal=GPIO_Output
PH4.Mode=I2C
PH4.Signal=I2C2_SCL
PH5.Mode=I2C
PH5.Signal=I2C2_SDA
PI10.Signal=GPIO_Output
PI2.Signal=S_TIM8_CH4
PI3.Signal=GPIO_Output
PI4.Signal=GPIO_Output
PI5.Signal=GPIO_Output
PI6.Signal=GPIO_Output
PI7.Signal=GPIO_Output
PI9.Signal=GPIO_Output
RCC.SYSCLKFreq_VALUE=64000000
board=custom

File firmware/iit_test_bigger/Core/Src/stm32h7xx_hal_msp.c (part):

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
    __HAL_RCC_GPIOB_CLK_ENABLE();
    /**I2C1 GPIO Configuration
    PB6     ------> I2C1_SCL
    PB7     ------> I2C1_SDA
    */
    GPIO_InitStruct.Pin = GPIO_PIN_6|GPIO_PIN_7;
    GPIO_InitStruct.Mode = GPIO_MODE_AF_OD;
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
    __HAL_RCC_GPIOH_CLK_ENABLE();
    /**I2C2 GPIO Configuration
    PH4     ------> I2C2_SCL
    PH5     ------> I2C2_SDA
    */
    GPIO_InitStruct.Pin = GPIO_PIN_4|GPIO_PIN_5;
    GPIO_InitStruct.Mode = GPIO_MODE_AF_OD;
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
    __HAL_RCC_GPIOH_CLK_ENABLE();
    /**I2C4 GPIO Configuration
    PH11     ------> I2C4_SCL
    PH12     ------> I2C4_SDA
    */
    GPIO_InitStruct.Pin = GPIO_PIN_11|GPIO_PIN_12;
    GPIO_InitStruct.Mode = GPIO_MODE_AF_OD;
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    __HAL_RCC_I2C1_CLK_DISABLE();

    /**I2C1 GPIO Configuration
    PB6     ------> I2C1_SCL
    PB7     ------> I2C1_SDA
    */
    HAL_GPIO_DeInit(GPIOB, GPIO_PIN_6);

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    __HAL_RCC_I2C2_CLK_DISABLE();

    /**I2C2 GPIO Configuration
    PH4     ------> I2C2_SCL
    PH5     ------> I2C2_SDA
    */
    HAL_GPIO_DeInit(GPIOH, GPIO_PIN_4);

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    __HAL_RCC_I2C4_CLK_DISABLE();

    /**I2C4 GPIO Configuration
    PH11     ------> I2C4_SCL
    PH12     ------> I2C4_SDA
    */
    HAL_GPIO_DeInit(GPIOH, GPIO_PIN_11);

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    __HAL_RCC_GPIOA_CLK_ENABLE();
    __HAL_RCC_GPIOG_CLK_ENABLE();
    /**I2S1 GPIO Configuration
    PA4     ------> I2S1_WS
    PA6     ------> I2S1_SDI
    PA7     ------> I2S1_SDO
    PG11     ------> I2S1_CK
    */
    GPIO_InitStruct.Pin = GPIO_PIN_4|GPIO_PIN_6|GPIO_PIN_7;
    GPIO_InitStruct.Mode = GPIO_MODE_AF_PP;
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    __HAL_RCC_SPI1_CLK_DISABLE();

    /**I2S1 GPIO Configuration
    PA4     ------> I2S1_WS
    PA6     ------> I2S1_SDI
    PA7     ------> I2S1_SDO
    PG11     ------> I2S1_CK
    */
    HAL_GPIO_DeInit(GPIOA, GPIO_PIN_4|GPIO_PIN_6|GPIO_PIN_7);

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
    __HAL_RCC_GPIOA_CLK_ENABLE();
    /**LPUART1 GPIO Configuration
    PA9     ------> LPUART1_TX
    PA10     ------> LPUART1_RX
    */
    GPIO_InitStruct.Pin = GPIO_PIN_9|GPIO_PIN_10;
    GPIO_InitStruct.Mode = GPIO_MODE_AF_PP;
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    __HAL_RCC_LPUART1_CLK_DISABLE();

    /**LPUART1 GPIO Configuration
    PA9     ------> LPUART1_TX
    PA10     ------> LPUART1_RX
    */
    HAL_GPIO_DeInit(GPIOA, GPIO_PIN_9|GPIO_PIN_10);

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    __HAL_RCC_GPIOC_CLK_ENABLE();
    __HAL_RCC_GPIOD_CLK_ENABLE();
    /**SDMMC1 GPIO Configuration
    PC8     ------> SDMMC1_D0
    PC9     ------> SDMMC1_D1
    PC10     ------> SDMMC1_D2
    PC11     ------> SDMMC1_D3
    PC12     ------> SDMMC1_CK
    PD2     ------> SDMMC1_CMD
    */
    GPIO_InitStruct.Pin = GPIO_PIN_8|GPIO_PIN_9|GPIO_PIN_10|GPIO_PIN_11
                          |GPIO_PIN_12;
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    __HAL_RCC_SDMMC1_CLK_DISABLE();

    /**SDMMC1 GPIO Configuration
    PC8     ------> SDMMC1_D0
    PC9     ------> SDMMC1_D1
    PC10     ------> SDMMC1_D2
    PC11     ------> SDMMC1_D3
    PC12     ------> SDMMC1_CK
    PD2     ------> SDMMC1_CMD
    */
    HAL_GPIO_DeInit(GPIOC, GPIO_PIN_8|GPIO_PIN_9|GPIO_PIN_10|GPIO_PIN_11
                          |GPIO_PIN_12);
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
    __HAL_RCC_GPIOI_CLK_ENABLE();
    /**TIM8 GPIO Configuration
    PI2     ------> TIM8_CH4
    */
    GPIO_InitStruct.Pin = GPIO_PIN_2;
    GPIO_InitStruct.Mode = GPIO_MODE_AF_PP;
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
    __HAL_RCC_GPIOA_CLK_ENABLE();
    /**USB_OTG_FS GPIO Configuration
    PA11     ------> USB_OTG_FS_DM
    PA12     ------> USB_OTG_FS_DP
    */
    GPIO_InitStruct.Pin = GPIO_PIN_11|GPIO_PIN_12;
    GPIO_InitStruct.Mode = GPIO_MODE_AF_PP;
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    __HAL_RCC_USB_OTG_FS_CLK_DISABLE();

    /**USB_OTG_FS GPIO Configuration
    PA11     ------> USB_OTG_FS_DM
    PA12     ------> USB_OTG_FS_DP
    */
    HAL_GPIO_DeInit(GPIOA, GPIO_PIN_11|GPIO_PIN_12);

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  __HAL_RCC_FMC_CLK_ENABLE();

  /** FMC GPIO Configuration
  PF0   ------> FMC_A0
  PF1   ------> FMC_A1
  PF2   ------> FMC_A2
  PF3   ------> FMC_A3
  PF4   ------> FMC_A4
  PF5   ------> FMC_A5
  PC0   ------> FMC_SDNWE
  PC2_C   ------> FMC_SDNE0
  PC3_C   ------> FMC_SDCKE0
  PF11   ------> FMC_SDNRAS
  PF12   ------> FMC_A6
  PF13   ------> FMC_A7
  PF14   ------> FMC_A8
  PF15   ------> FMC_A9
  PG0   ------> FMC_A10
  PG1   ------> FMC_A11
  PE7   ------> FMC_D4
  PE8   ------> FMC_D5
  PE9   ------> FMC_D6
  PE10   ------> FMC_D7
  PE11   ------> FMC_D8
  PE12   ------> FMC_D9
  PE13   ------> FMC_D10
  PE14   ------> FMC_D11
  PE15   ------> FMC_D12
  PD8   ------> FMC_D13
  PD9   ------> FMC_D14
  PD10   ------> FMC_D15
  PD14   ------> FMC_D0
  PD15   ------> FMC_D1
  PG4   ------> FMC_BA0
  PG5   ------> FMC_BA1
  PG8   ------> FMC_SDCLK
  PD0   ------> FMC_D2
  PD1   ------> FMC_D3
  PG15   ------> FMC_SDNCAS
  PE0   ------> FMC_NBL0
  PE1   ------> FMC_NBL1
  */
  GPIO_InitStruct.Pin = GPIO_PIN_0|GPIO_PIN_1|GPIO_PIN_2|GPIO_PIN_3
                          |GPIO_PIN_4|GPIO_PIN_5|GPIO_PIN_11|GPIO_PIN_12
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  __HAL_RCC_FMC_CLK_DISABLE();

  /** FMC GPIO Configuration
  PF0   ------> FMC_A0
  PF1   ------> FMC_A1
  PF2   ------> FMC_A2
  PF3   ------> FMC_A3
  PF4   ------> FMC_A4
  PF5   ------> FMC_A5
  PC0   ------> FMC_SDNWE
  PC2_C   ------> FMC_SDNE0
  PC3_C   ------> FMC_SDCKE0
  PF11   ------> FMC_SDNRAS
  PF12   ------> FMC_A6
  PF13   ------> FMC_A7
  PF14   ------> FMC_A8
  PF15   ------> FMC_A9
  PG0   ------> FMC_A10
  PG1   ------> FMC_A11
  PE7   ------> FMC_D4
  PE8   ------> FMC_D5
  PE9   ------> FMC_D6
  PE10   ------> FMC_D7
  PE11   ------> FMC_D8
  PE12   ------> FMC_D9
  PE13   ------> FMC_D10
  PE14   ------> FMC_D11
  PE15   ------> FMC_D12
  PD8   ------> FMC_D13
  PD9   ------> FMC_D14
  PD10   ------> FMC_D15
  PD14   ------> FMC_D0
  PD15   ------> FMC_D1
  PG4   ------> FMC_BA0
  PG5   ------> FMC_BA1
  PG8   ------> FMC_SDCLK
  PD0   ------> FMC_D2
  PD1   ------> FMC_D3
  PG15   ------> FMC_SDNCAS
  PE0   ------> FMC_NBL0
  PE1   ------> FMC_NBL1
  */
  HAL_GPIO_DeInit(GPIOF, GPIO_PIN_0|GPIO_PIN_1|GPIO_PIN_2|GPIO_PIN_3
                          |GPIO_PIN_4|GPIO_PIN_5|GPIO_PIN_11|GPIO_PIN_12
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
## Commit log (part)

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2026-03-30 research and pcb
2026-03-30 more pcb additions + research
2026-04-02 pcb i2c mux + connectors
2026-04-14 add sdram
2026-04-18 codec
2026-04-25 layout stuff
2026-04-26 board layout stuff
2026-04-26 create lcd footprint
2026-04-29 routed data bus of ram
2026-05-03 routed ram
2026-05-04 routed audio codec and sdram
2026-05-07 route connectors
2026-05-09 finish hacker header routing, drc checked
2026-05-09 silkscreen connectors
2026-05-12 length match sdram
2026-05-13 drc checks n more
2026-05-17 silkscreen for main board + finished sensor board
2026-05-26 add sensor and readme
2026-06-07 half ass implementation of tinyusb
2026-06-08 ok building it actually works w/o tinyusb
2026-06-08 fixed/added tinyusb to proj
2026-06-08 add i2c mux and neopixel hal libs
2026-06-08 actually add tinyusb correctly in cmake
2026-06-08 add tmag lib
2026-06-10 readme add stuff
2026-06-10 add jlcpcb carts and organize screenshots
2026-06-10 add bom
2026-06-11 add zine pdf
2026-06-22 add lcd level shifter, lm1117 ldo
2026-06-24 fix power scheme and add usb diode + more
2026-06-24 add stl
2026-06-28 remove production files
2026-06-28 add final prod files

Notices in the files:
firmware/iit_test_bigger/Core/Src/stm32h7xx_hal_msp.c:
Copyright (c) 2026 STMicroelectronics.
All rights reserved.
This software is licensed under terms that can be found in the LICENSE file
